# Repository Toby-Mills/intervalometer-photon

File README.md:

# intervalometer-photon

A Particle project named intervalometer-photon

## Welcome to your project!

Every new Particle project is composed of 3 important elements that you'll see have been created in your project directory for intervalometer-photon.

#### ```/src``` folder:  
This is the source folder that contains the firmware files for your project. It should *not* be renamed. 
Anything that is in this folder when you compile your project will be sent to our compile service and compiled into a firmware binary for the Particle device that you have targeted.

If your application contains multiple files, they should all be included in the `src` folder. If your firmware depends on Particle libraries, those dependencies are specified in the `project.properties` file referenced below.

#### ```.ino``` file:
This file is the firmware that will run as the primary application on your Particle device. It contains a `setup()` and `loop()` function, and can be written in Wiring or C/C++. For more information about using the Particle firmware API to create firmware for your Particle device, refer to the [Firmware Reference](https://docs.particle.io/reference/firmware/) section of the Particle documentation.

#### ```project.properties``` file:  
This is the file that specifies the name and version number of the libraries that your project depends on. Dependencies are added automatically to your `project.properties` file when you add a library to a project using the `particle library add` command in the CLI or add a library in the Desktop IDE.

## Adding additional files to your project

#### Projects with multiple sources
If you would like add additional files to your application, they should be added to the `/src` folder. All files in the `/src` folder will be sent to the Particle Cloud to produce a compiled binary.

#### Projects with external libraries
If your project includes a library that has not been registered in the Particle libraries system, you should create a new folder named `/lib/<libraryname>/src` under `/<project dir>` and add the `.h` and `.cpp` files for your library there. All contents of the `/lib` folder and subfolders will also be sent to the Cloud for compilation.

## Compiling your project

When you're ready to compile your project, make sure you have the correct Particle device target selected and run `particle compile <platform>` in the CLI or click the Compile button in the Desktop IDE. The following files in your project folder will be sent to the compile service:

- Everything in the `/src` folder, including your `.ino` application file
- The `project.properties` file for your project
- Any libraries stored under `lib/<libraryname>/src`

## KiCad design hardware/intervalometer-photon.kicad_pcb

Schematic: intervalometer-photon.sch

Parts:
D1: LED; LED_D5.0mm
J3: Conn_01x02; Pin_Header_Angled_1x02_Pitch2.54mm
R1: R; R_Axial_DIN0207_L6.3mm_D2.5mm_P7.62mm_Horizontal
SW1: SW_DIP_x01; TerminalBlock_bornier-2_P5.08mm
U1: LTV-827; DIP-8_W7.62mm
U2: Photon; photon_tht

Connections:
3V3: U2.24
GND: D1.1, SW1.1, U2.21
unnamed: D1.2, U1.2
unnamed: J3.1, U1.8
unnamed: J3.2, U1.7
unnamed: R1.1, U1.1
OPTO: R1.2, U2.14
START: SW1.2, U2.19

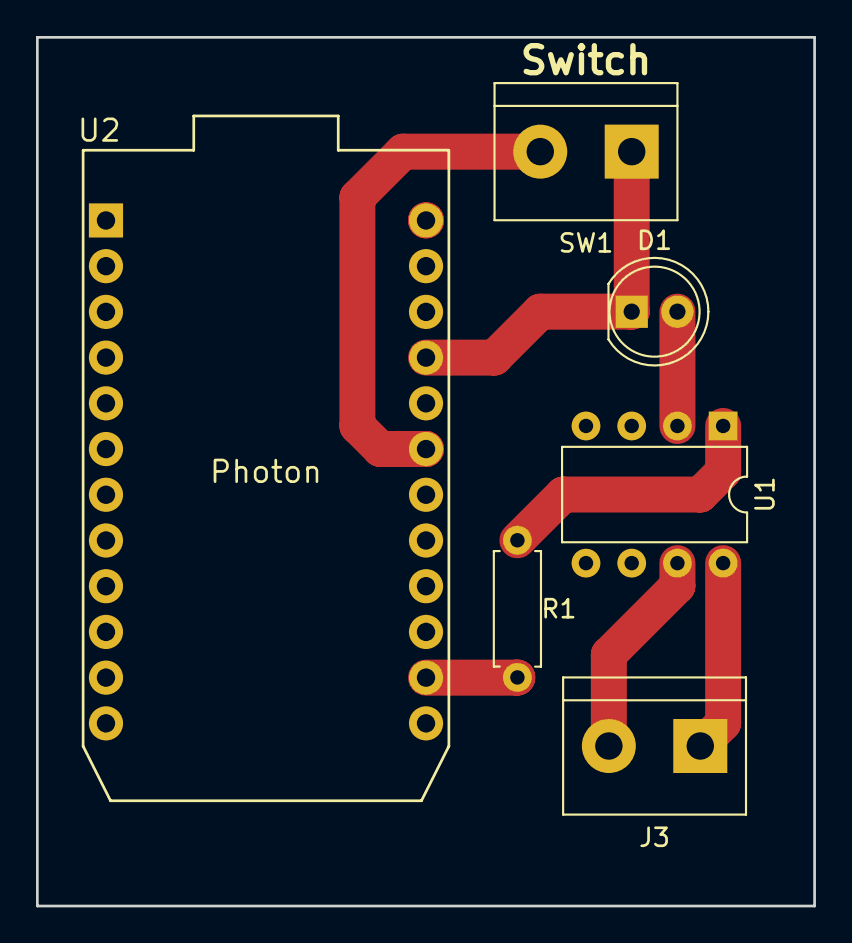
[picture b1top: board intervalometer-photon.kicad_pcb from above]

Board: 2 copper layers, 43.2 x 48.3 mm, 6 parts (0 on the bottom side), 7 nets.

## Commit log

2018-08-13 Cloud Variable 'sourceCode' to return URL to github repo
2018-08-15 Initial hardware design work
2018-08-16 bug fixes & syntax
2018-08-16 Renamed 'mode' to 'phase' & added MirrorLockupBuffer phase
2018-08-16 Registered additional cloud variables
2018-08-16 Bug fix checking last photo time
2018-08-16 Git ignore bin files
2018-08-17 Added debugging message capability
2018-08-17 improved legibility by using functions to manage Phase
2018-08-17 Enabled SYSTEM_THREAD to allow network connection in separate thread
2018-08-17 Moved enum declarations
2018-08-17 Fixed compile errors for cloud debugging function
2018-08-17 Code layout changes
2018-08-17 Moved functions up to avoid scope problems
2018-08-17 Bug Fix
2018-08-17 Additional debugging info
2018-08-20 Added support for switch to start / end activity
2018-10-13 Changed switch to use Pin D6, with buit in pull down resistor
2019-05-08 Moved to Particle Workbench
2019-05-08 Added debug messages & changed default exposure
2019-05-08 updated hardware schematics
2019-05-08 updated to ignore build artefact
2021-01-28 updated firmware to 2.0.1
2021-01-28 Added Blynk integration
2021-02-01 refactored to not include token in code
